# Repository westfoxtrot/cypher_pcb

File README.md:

# cypher PCB
Custom PCB that was designed for the cypher board (Case files coming soon once confirmed functional)

It is a F-keyless Compact 1800

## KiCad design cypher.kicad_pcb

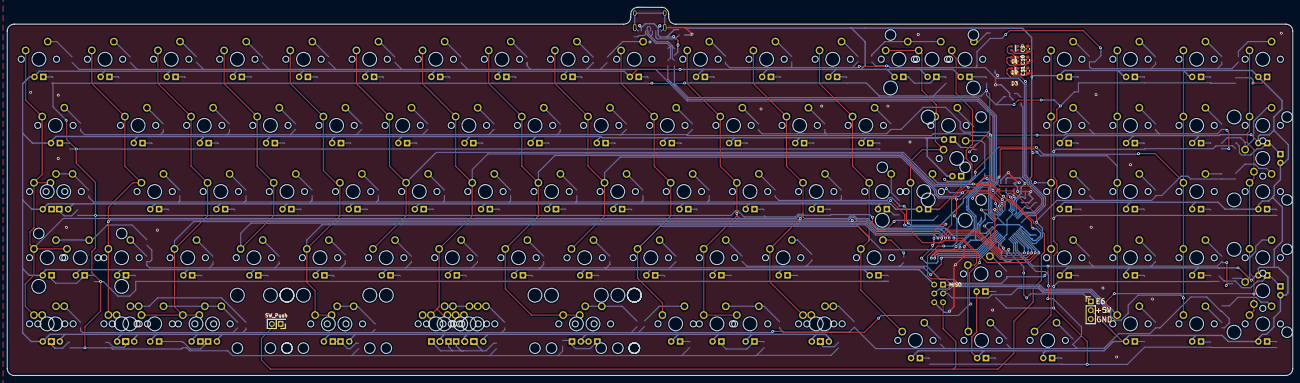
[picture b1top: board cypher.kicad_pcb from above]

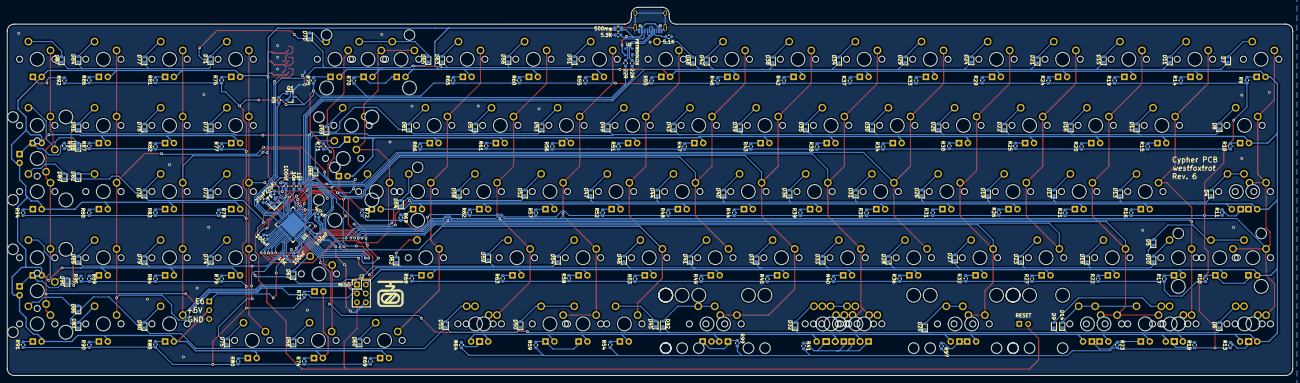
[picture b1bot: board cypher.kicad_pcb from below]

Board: 2 copper layers, 370.1 x 106.0 mm, 313 parts (199 on the bottom side), 217 nets.

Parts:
C1: 4.7uF; C_0603_1608Metric
C2, C3: 22pF; C_0603_1608Metric
C4, C5, C6, C7: 100nF; C_0603_1608Metric
C8: 1uf; C_0603_1608Metric
C9, C10, C11: 100nf; C_0603_1608Metric
D1, D2, D3: WS2812B; WS2812-2020
D4, D5, D6, D7, D8, D9, D10, D11, D12, D13, D14, D15, D16, D17, D18, D19, D20, D21, D22, D23, D24, D25, D26, D27, D28, D29, D30, D31, D32, D33, D34, D35, D36, D37, D38, D39, D40, D41, D42, D43, D44, D45, D46, D47, D48, D49, D50, D51, D52, D53, D54, D55, D56, D57, D58, D59, D60, D61, D62, D63, D64, D65, D66, D67, D68, D69, D70, D71, D72, D73, D74, D75, D76, D77, D78, D79, D80, D81, D82, D83, D84, D85, D86, D87, D88, D89, D90, D92: 1N4148; D_0603_1608Metric
F1: 500ma; Fuse_0805_2012Metric
J2: AVR-ISP-6; PinHeader_2x03_P2.54mm_Vertical
J3: Breakout; PinHeader_1x03_P2.54mm_Vertical
MX1: ANSI Shift; MXOnly-2.25U
MX2: Control 7u; MXOnly-1.5U-FLIPPED
MX3: STEPPED CAPS; MXOnly-1.25U
MX4: Esc; MXOnly-1U
MX5: Tab; MXOnly-1.5U
MX6: CAPS; MXOnly-1.75U-FLIPPED
MX7: ISO Shift; MXOnly-1.25U
MX8: Control 6u/6.25u; MXOnly-1.25U
MX9: Super 6.25u; MXOnly-1U-FLIPPED
MX10: 1; MXOnly-1U
MX11: Q; MXOnly-1U
MX12: A; MXOnly-1U
MX13: ISO_BS; MXOnly-1U
MX14: Super 6u; MXOnly-1U
MX15: Alt 7u; MXOnly-1.5U
MX16: 2; MXOnly-1U
MX17: W; MXOnly-1U
MX18: S; MXOnly-1U
MX19: Z; MXOnly-1U
MX20: Alt 6u; MXOnly-1.25U
MX21: 3; MXOnly-1U
MX22: E; MXOnly-1U
MX23: D; MXOnly-1U
MX24: X; MXOnly-1U
MX25: Alt 6.25u; MXOnly-1.25U-FLIPPED
MX26: 4; MXOnly-1U
MX27: R; MXOnly-1U
MX28: F; MXOnly-1U
MX29: C; MXOnly-1U
MX30: 5; MXOnly-1U
MX31: T; MXOnly-1U
MX32: G; MXOnly-1U
MX33: V; MXOnly-1U
MX34: Space 6.25u; MXOnly-6.25U-FLIPPED-ReversedStabilizers
MX35: Space 7u; MXOnly-7U-FLIPPED-ReversedStabilizers
MX36: 6; MXOnly-1U
MX37: Y; MXOnly-1U
MX38: H; MXOnly-1U
MX39: B; MXOnly-1U
MX40: Space 6u; MXOnly-6U-ReversedStabilizers
MX41: 7; MXOnly-1U
MX42: U; MXOnly-1U
MX43: J; MXOnly-1U
MX44: N; MXOnly-1U
MX45: 8; MXOnly-1U
MX46: I; MXOnly-1U
MX47: K; MXOnly-1U
MX48: M; MXOnly-1U
MX49: 9; MXOnly-1U
MX50: O; MXOnly-1U
MX51: L; MXOnly-1U
MX52: ,; MXOnly-1U
MX53: RAlt 6u; MXOnly-1.25U
MX54: Ralt 6.25u/7u; MXOnly-1.5U
MX55: 0; MXOnly-1U
MX56: P; MXOnly-1U
MX57: ;; MXOnly-1U
MX58: .; MXOnly-1U
MX59: RSuper 6u; MXOnly-1U
MX60: Fn 6.25u/7u; MXOnly-1.5U
MX61: -; MXOnly-1U
MX62: [; MXOnly-1U
MX63: '; MXOnly-1U
MX64: /; MXOnly-1U
MX65: Fn 6u; MXOnly-1.25U-FLIPPED
MX66: =; MXOnly-1U
MX67: ]; MXOnly-1U
MX68: ISO Hash; MXOnly-1U
MX69: Shift; MXOnly-1.75U
MX70: Left; MXOnly-1U
MX71: Split Backspace Left; MXOnly-1U
MX72: ISO Enter; MXOnly-ISO-ReversedStabilizers
MX73: Backspace; MXOnly-2U
MX74: Backslash; MXOnly-1.5U
MX75: ANSI Enter; MXOnly-2.25U
MX76: Up; MXOnly-1U
MX77: Down; MXOnly-1U
MX78: Split Backspace Right; MXOnly-1U
MX79: Num Lock; MXOnly-1U
MX80: Num 7; MXOnly-1U
MX81: Num 4; MXOnly-1U
MX82: Num 1; MXOnly-1U
MX83: Right; MXOnly-1U
MX84: Num /; MXOnly-1U
MX85: Num 8; MXOnly-1U
MX86: Num 5; MXOnly-1U
MX87: Num 2; MXOnly-1U
MX88: Num 0; MXOnly-1U
MX89: Num *; MXOnly-1U
MX90: Num 9; MXOnly-1U
MX91: Num 6; MXOnly-1U
MX92: Num 3; MXOnly-1U
MX93: Num .; MXOnly-1U
MX94: Num + 1u; MXOnly-1U
MX95: Num Enter 1u; MXOnly-1U
MX96: Num Backspace; MXOnly-1U
MX97: Num -; MXOnly-1U
MX98: Num +; MXOnly-2U-ReversedStabilizers
MX99: Num =; MXOnly-1U
MX100: Num Enter; MXOnly-2U-ReversedStabilizers
MX101: Split_left; MXOnly-2.75U-FLIPPED-ReversedStabilizers
MX102: Split_left; MXOnly-2.25U-ReversedStabilizers
MX103: Split_center; MXOnly-1.25U
MX104: Split_center; MXOnly-1.25U-FLIPPED
MX105: Split_right; MXOnly-2.25U-ReversedStabilizers
MX106: Split_right; MXOnly-2.75U-FLIPPED-ReversedStabilizers
Q1: MMBT3904; SOT-23
R1, R2: 22R; R_0603_1608Metric
R3: 10k; R_0603_1608Metric
R4: 10K; R_0603_1608Metric
R5: 1.5K; R_0603_1608Metric
R9, R10, R11, R12, R13, R14, R15, R16, R17, R18, R19, R20, R21, R22, R23, R24, R25, R26, R27, R29, R30, R31, R32, R33, R34, R35, R36, R37, R38, R39, R40, R41, R42, R43, R44, R45, R46, R47, R48, R49, R50, R51, R52, R53, R54, R55, R56, R57, R58, R59, R60, R61, R62, R63, R64, R65, R66, R67, R68, R69, R70, R71, R72, R73, R74, R75, R76, R77, R78, R79, R80, R81, R82, R83, R84, R85, R86, R87, R88, R89, R90, R91, R92, R93, R94, R95, R97, R99: 470; R_0603_1608Metric
R28, R96: 5.1K; R_0603_1608Metric
SW1: SW_Push; PinHeader_2x01_P2.54mm_Vertical
U1: ATmega32U4-MU; QFN-44-1EP_7x7mm_P0.5mm_EP5.2x5.2mm
U2: PRTR5V0U2X; SOT143B
USB1: HRO-TYPE-C-31-M-12
Y1: 16Mhz; Crystal_SMD_2520-4Pin_2.5x2.0mm
svg2mod: G***; CableCarLogo

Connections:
+5V: C1.2, C4.2, C5.2, C6.2, C7.2, C9.1, C10.1, C11.1, D1.1, D2.1, D3.1, F1.1, J2.2, J3.2, MX1.3, MX2.3, MX3.3, MX4.3, MX5.3, MX6.3, MX7.3, MX8.3, MX9.3, MX10.3, MX11.3, MX12.3, MX13.3, MX14.3, MX15.3, MX16.3, MX17.3, MX18.3, MX19.3, MX20.3, MX21.3, MX22.3, MX23.3, MX24.3, MX25.3, MX26.3, MX27.3, MX28.3, MX29.3, MX30.3, MX31.3, MX32.3, MX33.3, MX34.3, MX35.3, MX36.3, MX37.3, MX38.3, MX39.3, MX40.3, MX41.3, MX42.3, MX43.3, MX44.3, MX45.3, MX46.3, MX47.3, MX48.3, MX49.3, MX50.3, MX51.3, MX52.3, MX53.3, MX54.3, MX55.3, MX56.3, MX57.3, MX58.3, MX59.3, MX60.3, MX61.3, MX62.3, MX63.3, MX64.3, MX65.3, MX66.3, MX67.3, MX68.3, MX69.3, MX70.3, MX71.3, MX72.3, MX73.3, MX74.3, MX75.3, MX76.3, MX77.3, MX78.3, MX79.3, MX80.3, MX81.3, MX82.3, MX83.3, MX84.3, MX85.3, MX86.3, MX87.3, MX88.3, MX89.3, MX90.3, MX91.3, MX92.3, MX93.3, MX94.3, MX95.3, MX96.3, MX97.3, MX98.3, MX99.3, MX100.3, MX101.3, MX102.3, MX103.3, MX104.3, MX105.3, MX106.3, R3.2, U1.2, U1.7, U1.14, U1.24, U1.34, U1.44
Caps: D3.4, U1.22
Col0: MX1.1, MX2.1, MX3.1, MX4.1, MX5.1, MX6.1, MX7.1, MX8.1, MX54.1, MX55.1, MX56.1, MX57.1, MX58.1, MX59.1, U1.26
Col1: MX9.1, MX10.1, MX11.1, MX12.1, MX13.1, MX14.1, MX60.1, MX61.1, MX62.1, MX63.1, MX64.1, MX65.1, U1.27
Col2: MX15.1, MX16.1, MX17.1, MX18.1, MX19.1, MX20.1, MX25.1, MX66.1, MX67.1, MX68.1, MX69.1, MX70.1, U1.28
Col3: MX21.1, MX22.1, MX23.1, MX24.1, MX71.1, MX72.1, MX73.1, MX74.1, MX75.1, MX76.1, MX77.1, U1.29
Col4: MX26.1, MX27.1, MX28.1, MX29.1, MX78.1, MX101.1, MX102.1, U1.30
Col5: MX30.1, MX31.1, MX32.1, MX33.1, MX79.1, MX80.1, MX81.1, MX82.1, MX83.1, U1.12
Col6: J2.1, MX34.1, MX35.1, MX36.1, MX37.1, MX38.1, MX39.1, MX40.1, MX84.1, MX85.1, MX86.1, MX87.1, MX88.1, MX103.1, MX104.1, U1.11
Col7: J2.4, MX41.1, MX42.1, MX43.1, MX44.1, MX89.1, MX90.1, MX91.1, MX92.1, MX93.1, MX105.1, MX106.1, U1.10
Col8: J2.3, MX45.1, MX46.1, MX47.1, MX48.1, MX94.1, MX95.1, MX96.1, MX97.1, MX98.1, MX99.1, MX100.1, U1.9
Col9: MX49.1, MX50.1, MX51.1, MX52.1, MX53.1, U1.41
D+: R2.1, U1.4
D-: R1.1, U1.3
E6: J3.1, U1.1
GND: C1.1, C2.2, C3.2, C4.1, C5.1, C6.1, C7.1, C8.2, C9.2, C10.2, C11.2, D1.3, D2.3, D3.3, J2.6, J3.3, Q1.2, R4.1, R28.2, R96.2, SW1.1, U1.5, U1.15, U1.23, U1.35, U1.43, U1.45, U2.1, USB1.1, USB1.12, USB1.13, Y1.2, Y1.4
LEDGND: Q1.3, R9.2, R10.2, R11.2, R12.2, R13.2, R14.2, R15.2, R16.2, R17.2, R18.2, R19.2, R20.2, R21.2, R22.2, R23.2, R24.2, R25.2, R26.2, R27.2, R29.2, R30.2, R31.2, R32.2, R33.2, R34.2, R35.2, R36.2, R37.2, R38.2, R39.2, R40.2, R41.2, R42.2, R43.2, R44.2, R45.2, R46.2, R47.2, R48.2, R49.2, R50.2, R51.2, R52.2, R53.2, R54.2, R55.2, R56.2, R57.2, R58.2, R59.2, R60.2, R61.2, R62.2, R63.2, R64.2, R65.2, R66.2, R67.2, R68.2, R69.2, R70.2, R71.2, R72.2, R73.2, R74.2, R75.2, R76.2, R77.2, R78.2, R79.2, R80.2, R81.2, R82.2, R83.2, R84.2, R85.2, R86.2, R87.2, R88.2, R89.2, R90.2, R91.2, R92.2, R93.2, R94.2, R95.2, R97.2, R99.2
unnamed: C8.1, U1.6
unnamed: D1.4, D2.2
unnamed: D2.4, D3.2
unnamed: D4.2, MX3.2, MX6.2
unnamed: D5.2, MX1.2, MX7.2
unnamed: D6.2, MX2.2, MX8.2
unnamed: D7.2, MX4.2
unnamed: D8.2, MX5.2
unnamed: D9.2, MX9.2, MX14.2
unnamed: D10.2, MX13.2
unnamed: D11.2, MX10.2
unnamed: D12.2, MX11.2
unnamed: D13.2, MX12.2
unnamed: D14.2, MX15.2, MX20.2, MX25.2
unnamed: D15.2, MX16.2
unnamed: D16.2, MX17.2
unnamed: D17.2, MX18.2
unnamed: D18.2, MX19.2
unnamed: D19.2, MX23.2
unnamed: D20.2, MX101.2, MX102.2
unnamed: D21.2, MX21.2
unnamed: D22.2, MX22.2
unnamed: D23.2, MX24.2
unnamed: D24.2, MX26.2
unnamed: D25.2, MX27.2
unnamed: D26.2, MX28.2
unnamed: D27.2, MX29.2
unnamed: D28.2, MX33.2
unnamed: D29.2, MX30.2
unnamed: D30.2, MX31.2
unnamed: D31.2, MX32.2
unnamed: D32.2, MX34.2, MX35.2, MX40.2, MX103.2, MX104.2
unnamed: D33.2, MX39.2
unnamed: D34.2, MX36.2
unnamed: D35.2, MX37.2
unnamed: D36.2, MX38.2
unnamed: D37.2, MX44.2
unnamed: D38.2, MX41.2
unnamed: D39.2, MX42.2
unnamed: D40.2, MX43.2
unnamed: D41.2, MX48.2
unnamed: D42.2, MX45.2
unnamed: D43.2, MX46.2
unnamed: D44.2, MX47.2
unnamed: D45.2, MX53.2
unnamed: D46.2, MX52.2
unnamed: D47.2, MX51.2
unnamed: D48.2, MX49.2
unnamed: D49.2, MX50.2
unnamed: D50.2, MX54.2, MX59.2
unnamed: D51.2, MX55.2
unnamed: D52.2, MX57.2
unnamed: D53.2, MX56.2
unnamed: D54.2, MX58.2
unnamed: D55.2, MX60.2, MX65.2
unnamed: D56.2, MX61.2
unnamed: D57.2, MX62.2
unnamed: D58.2, MX63.2
unnamed: D59.2, MX64.2
unnamed: D60.2, MX70.2
unnamed: D61.2, MX67.2
unnamed: D62.2, MX69.2
unnamed: D63.2, MX66.2
unnamed: D64.2, MX68.2
unnamed: D65.2, MX71.2, MX73.2
unnamed: D66.2, MX72.2, MX75.2
unnamed: D67.2, MX76.2
unnamed: D68.2, MX77.2
unnamed: D69.2, MX74.2
unnamed: D70.2, MX78.2
unnamed: D71.2, MX79.2
unnamed: D72.2, MX81.2
unnamed: D73.2, MX80.2
unnamed: D74.2, MX82.2
unnamed: D75.2, MX83.2
unnamed: D76.2, MX86.2
unnamed: D77.2, MX84.2
unnamed: D78.2, MX85.2
unnamed: D79.2, MX87.2
unnamed: D80.2, MX88.2
unnamed: D81.2, MX90.2
unnamed: D82.2, MX91.2
unnamed: D83.2, MX93.2
unnamed: D84.2, MX89.2
unnamed: D85.2, MX92.2
unnamed: D86.2, MX96.2
unnamed: D87.2, MX97.2
unnamed: D88.2, MX94.2, MX98.2
unnamed: D89.2, MX99.2
unnamed: D90.2, MX95.2, MX100.2
unnamed: D92.2, MX105.2, MX106.2
unnamed: MX1.4, MX7.4, R12.1
unnamed: MX2.4, MX8.4, R13.1
unnamed: MX3.4, MX6.4, R11.1
unnamed: MX4.4, R9.1
unnamed: MX5.4, R10.1
unnamed: MX10.4, R14.1
unnamed: MX11.4, R15.1
unnamed: MX12.4, R16.1
unnamed: MX13.4, R17.1
unnamed: MX9.4, MX14.4, R18.1
unnamed: MX15.4, MX20.4, MX25.4, R23.1
unnamed: MX16.4, R19.1
unnamed: MX17.4, R20.1
unnamed: MX18.4, R21.1
unnamed: MX19.4, R22.1
unnamed: MX21.4, R24.1
unnamed: MX22.4, R25.1
unnamed: MX23.4, R26.1
unnamed: MX24.4, R27.1
unnamed: MX26.4, R29.1
unnamed: MX27.4, R30.1
unnamed: MX28.4, R31.1
unnamed: MX29.4, R32.1
unnamed: MX30.4, R33.1
unnamed: MX31.4, R34.1
unnamed: MX32.4, R35.1
unnamed: MX33.4, R36.1
unnamed: MX36.4, R37.1
unnamed: MX37.4, R38.1
unnamed: MX38.4, R39.1
unnamed: MX39.4, R40.1
unnamed: MX41.4, R42.1
unnamed: MX42.4, R43.1
unnamed: MX43.4, R44.1
unnamed: MX44.4, R45.1
unnamed: MX45.4, R46.1
unnamed: MX46.4, R47.1
unnamed: MX47.4, R48.1
unnamed: MX48.4, R49.1
unnamed: MX49.4, R50.1
unnamed: MX50.4, R51.1
unnamed: MX51.4, R52.1
unnamed: MX52.4, R53.1
unnamed: MX53.4, R54.1
unnamed: MX54.4, MX59.4, R59.1
unnamed: MX55.4, R55.1
unnamed: MX56.4, R56.1
unnamed: MX57.4, R57.1
unnamed: MX58.4, R58.1
unnamed: MX60.4, MX65.4, R64.1
unnamed: MX61.4, R60.1
unnamed: MX62.4, R61.1
unnamed: MX63.4, R62.1
unnamed: MX64.4, R63.1
unnamed: MX66.4, R65.1
unnamed: MX67.4, R66.1
unnamed: MX68.4, R67.1
unnamed: MX69.4, R68.1
unnamed: MX70.4, R69.1
unnamed: MX71.4, MX73.4, R70.1
unnamed: MX72.4, MX75.4, R72.1
unnamed: MX74.4, R71.1
unnamed: MX76.4, R73.1
unnamed: MX77.4, R74.1
unnamed: MX78.4, R75.1
unnamed: MX79.4, R76.1
unnamed: MX80.4, R77.1
unnamed: MX81.4, R78.1
unnamed: MX82.4, R79.1
unnamed: MX83.4, R80.1
unnamed: MX84.4, R81.1
unnamed: MX85.4, R82.1
unnamed: MX86.4, R83.1
unnamed: MX87.4, R84.1
unnamed: MX88.4, R85.1
unnamed: MX89.4, R86.1
unnamed: MX90.4, R87.1
unnamed: MX91.4, R88.1
unnamed: MX92.4, R89.1
unnamed: MX93.4, R90.1
unnamed: MX94.4, MX98.4, R93.1
unnamed: MX96.4, R91.1
unnamed: MX97.4, R92.1
unnamed: MX99.4, R94.1
unnamed: MX95.4, MX100.4, R95.1
unnamed: MX101.4, MX102.4, R97.1
unnamed: MX34.4, MX35.4, MX40.4, MX103.4, MX104.4, R41.1
unnamed: MX105.4, MX106.4, R99.1
unnamed: Q1.1, R5.1
unnamed: R1.2, U2.2, USB1.5, USB1.7
unnamed: R2.2, U2.3, USB1.6, USB1.8
unnamed: R4.2, U1.33
unnamed: R5.2, U1.18
unnamed: R28.1, USB1.4
unnamed: R96.1, USB1.10
RESET: J2.5, R3.1, SW1.2, U1.13
Row0: D7.1, D11.1, D15.1, D21.1, D24.1, D29.1, D34.1, D38.1, D42.1, D48.1, U1.8
Row1: D8.1, D12.1, D16.1, D22.1, D25.1, D30.1, D35.1, D39.1, D43.1, D49.1, U1.40
Row2: D4.1, D13.1, D17.1, D19.1, D26.1, D31.1, D36.1, D40.1, D44.1, D47.1, U1.38
Row3: D5.1, D10.1, D18.1, D23.1, D27.1, D28.1, D33.1, D37.1, D41.1, D46.1, U1.37
Row4: D6.1, D9.1, D14.1, D20.1, D32.1, D45.1, D92.1, U1.36
Row5: D51.1, D56.1, D63.1, D65.1, D70.1, D71.1, D77.1, D84.1, D87.1, U1.19
Row6: D53.1, D57.1, D61.1, D69.1, D73.1, D78.1, D81.1, D88.1, U1.39
Row7: D52.1, D58.1, D64.1, D66.1, D72.1, D76.1, D82.1, D89.1, U1.25
Row8: D54.1, D59.1, D62.1, D67.1, D74.1, D79.1, D85.1, D90.1, U1.31
Row9: D50.1, D55.1, D60.1, D68.1, D75.1, D80.1, D83.1, D86.1, U1.32
VCC: F1.2, U2.4, USB1.2, USB1.11
XTAL1: C2.1, U1.17, Y1.1
XTAL2: C3.1, U1.16, Y1.3

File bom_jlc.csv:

Designator,Comment,Footprint,LCSC Part Number
C2,10nf,C_0603_1608Metric,C57112 
C5 C6 C7 C8 C9 C10 C11,100nF,C_0603_1608Metric,C1591 
C1 C4,4.7uF,C_0603_1608Metric,C19666 
C3,10uf,C_0603_1608Metric,C96446 
D4 D5 D6 D7 D8 D9 D10 D11 D12 D13 D14 D15 D16 D17 D18 D19 D20 D21 D22 D23 D24 D25 D26 D27 D28 D29 D30 D31 D32 D33 D34 D35 D36 D37 D38 D39 D40 D41 D42 D43 D44 D45 D46 D47 D48 D49 D50 D51 D52 D53 D54 D55 D56 D57 D58 D59 D60 D61 D62 D63 D64 D65 D66 D67 D68 D69 D70 D71 D72 D73 D74 D75 D76 D77 D78 D79 D80 D81 D82 D83 D84 D85 D86 D87 D88 D89 D90 D92 D93 D94 D95 D96,1N4148,D_SOD-123,C81598 
D91,BAT54T1G,D_SOD-123,C152458 
D1 D2 D3,WS2812B,WS2812-2020,C965555 
F1,ASMD1206-050,Fuse_1206_3216Metric,C135338 
L1,MLB3216-600P4A,L_1206_3216Metric,C33600 
Q1,BC850,SOT-23,C78484 
Q2,MMBT3904,SOT-23,C20526 
R3 R4 R6 R7 R9 R10 R11 R12 R13 R14 R15 R16 R17 R18 R19 R20 R21 R22 R23 R24 R25 R26 R27 R29 R30 R31 R32 R33 R34 R35 R36 R37 R38 R39 R40 R41 R42 R43 R44 R45 R46 R47 R48 R49 R50 R51 R52 R53 R54 R55 R56 R57 R58 R59 R60 R61 R62 R63 R64 R65 R66 R67 R68 R69 R70 R71 R72 R73 R74 R75 R76 R77 R78 R79 R80 R81 R82 R83 R84 R85 R86 R87 R88 R89 R90 R91 R92 R93 R94 R95 R97 R99,470,R_0603_1608Metric,C23179 
R1 R5,1.5k,R_0603_1608Metric,C22843 
R28 R96,5.1K,R_0603_1608Metric,C23186 
R8,10k,R_0603_1608Metric,C98220 
R2,30k,R_0603_1608Metric,C22984 
SP1,UCLAMP0571P.TNT,SGP1610N2,C512387 
U3,LD3985G33R_TSOT23,TSOT-23-5,C46243 
U1,STM32F072CBTx,LQFP-48_7x7mm_P0.5mm,C81720 
U4,TXS0101DBV,SOT-23-6,C132604 
U2,USBLC6-2P6,SOT-666,C2827693 
USB1,HRO-TYPE-C-31-M-12,HRO-TYPE-C-31-M-12,C165948

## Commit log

2018-12-28 Commit of current design
2018-12-28 Update files to rev. 2
    correction of error in the crystal wiring
    adjusted all the diode footprints to be easier to read
    moved D70 to be vertical and placed more in line with the rest of the diodes
    bumped silkscreen to rev. 2
2018-12-28 Updated gerber and readme
2019-02-23 updated to rev.3
2019-10-24 update to rev5
2020-04-24 updated to rev 5.1
2020-04-26 Added base for Rev 6
2020-04-26 Rerouted, added render
2020-05-17 updated rev6
2020-08-09 cleanup of files - added bom in csv
2021-03-31 updated to latest rev
2021-04-20 Cleanup and commit for rev6
2022-07-24 update to latest rev7
2022-07-24 adjusts solder mask clearance
2022-07-24 update gerber
2022-07-26 updates ESD and reset circuit
2022-07-27 update to rev7
2022-08-06 Updated incorrect part no
2022-08-06 Added JLC bom
